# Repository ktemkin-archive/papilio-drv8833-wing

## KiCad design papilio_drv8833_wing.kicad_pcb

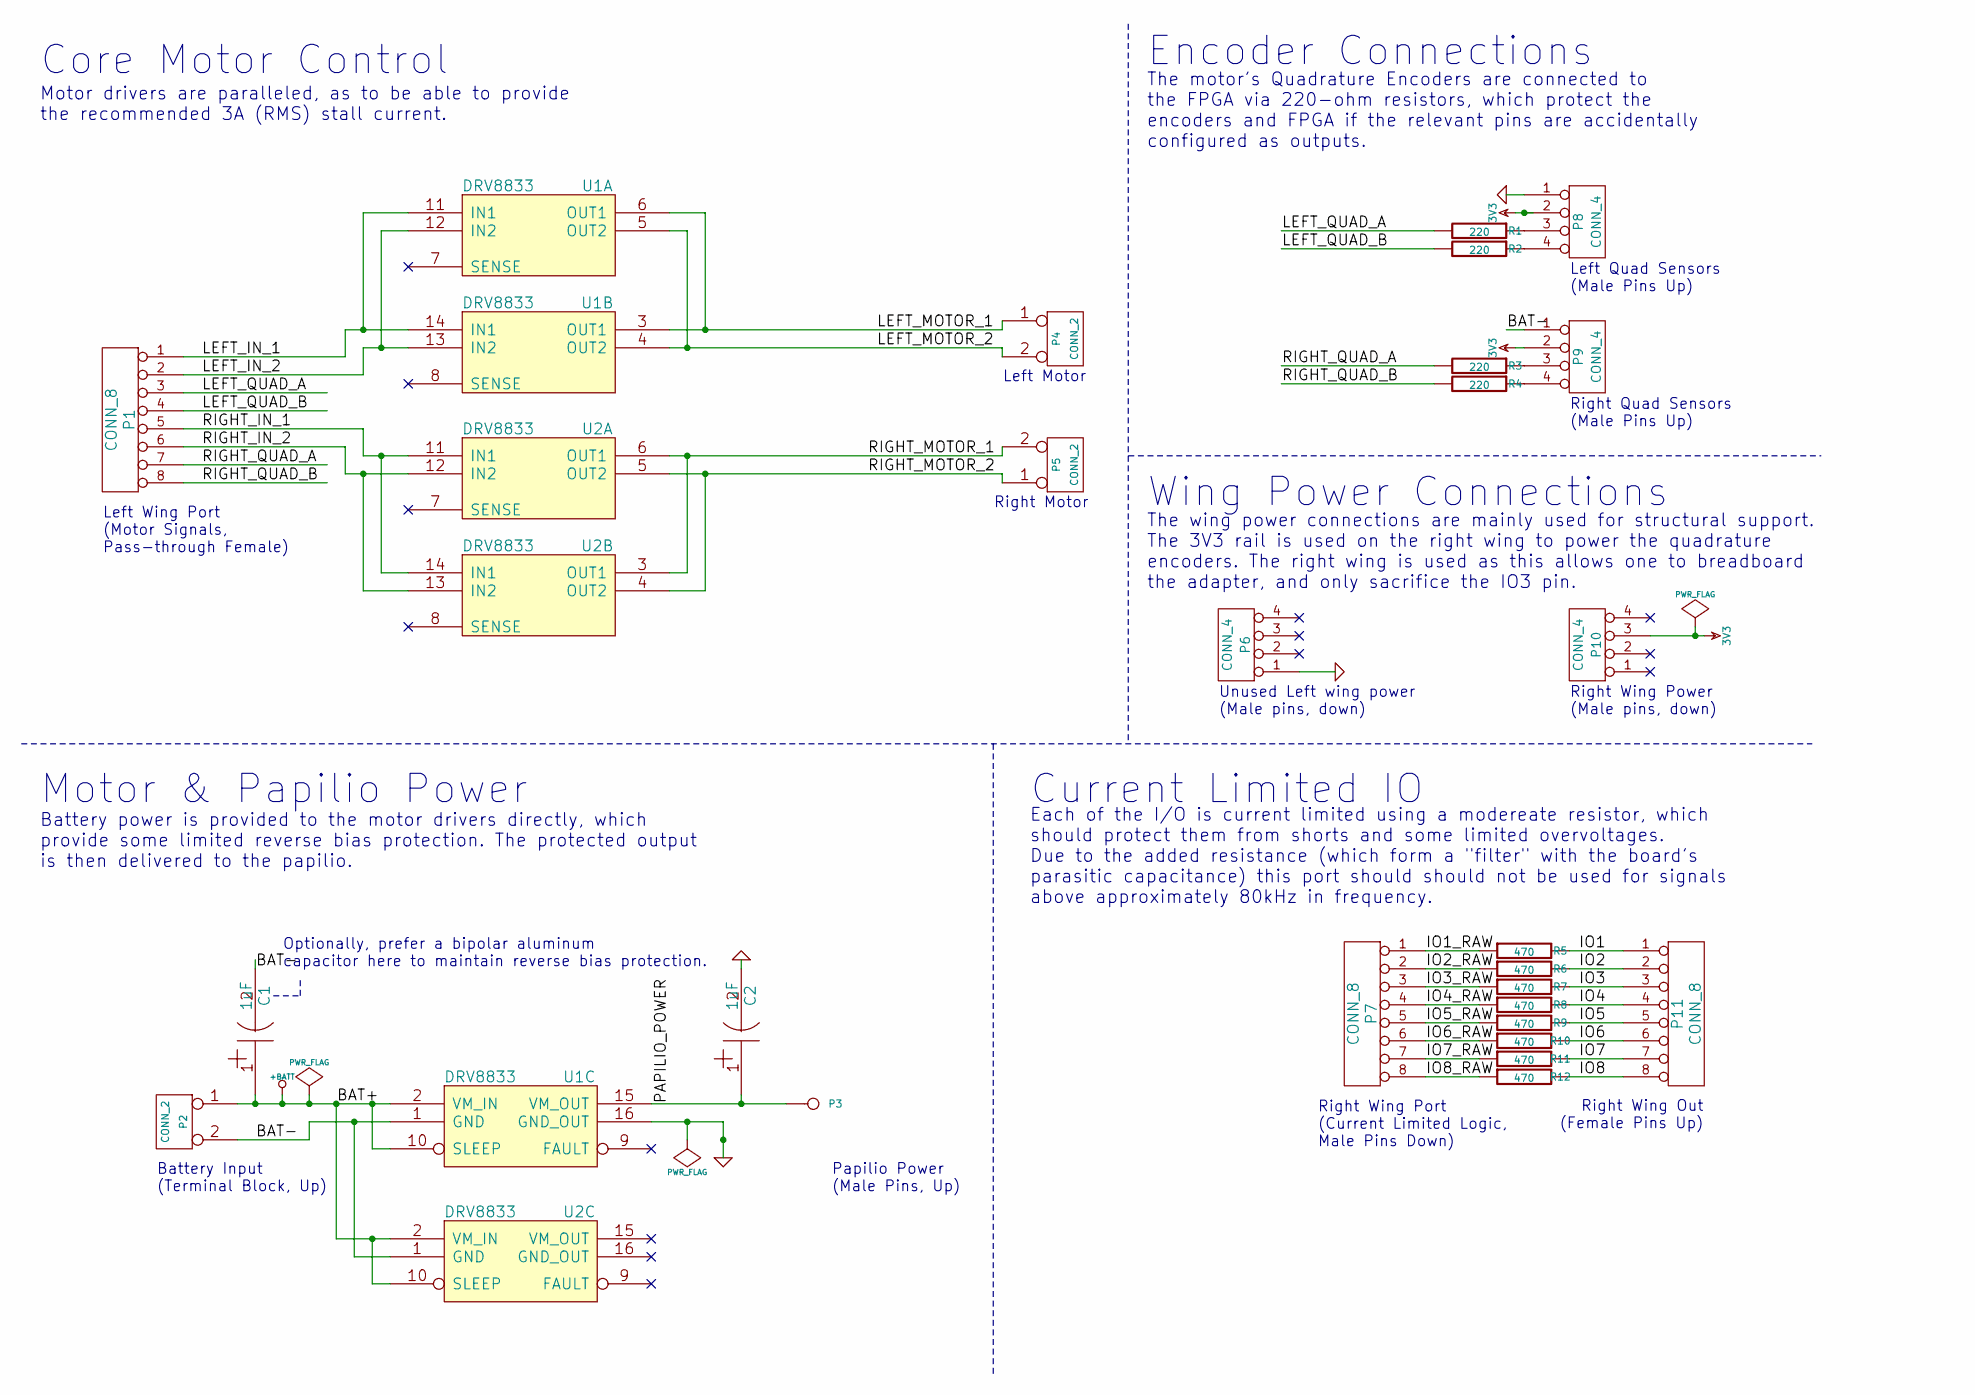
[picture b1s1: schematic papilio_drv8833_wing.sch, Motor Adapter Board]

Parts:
C1, C2: 1uF; Capacitor5x11RM2.5
P1, P7, P11: CONN_8; SIL-8
P2: CONN_2; terminal-block-D021B01LF
P3: CONN_1; SIL-1
P4, P5: CONN_2; rover5-motor
P6, P8, P9, P10: CONN_4; SIL-4
R1, R2, R3, R4: 220; Resistor_Horizontal_RM10mm
R5, R6, R7, R8, R9, R10, R11, R12: 470; Resistor_Horizontal_RM10mm
U1, U2: DRV8833; DRV8833-carrier

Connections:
3V3: P8.2, P9.2, P10.3
+BATT: C1.1, P2.1, U1.2 (VM_IN), U1.10 (SLEEP), U2.2 (VM_IN), U2.10 (SLEEP)
/BAT-: C1.2, P2.2 (PM), P9.1, U1.1 (GND), U2.1 (GND)
/IO1: P11.1, R5.2
/IO1_RAW: P7.1, R5.1
/IO2: P11.2, R6.2
/IO2_RAW: P7.2, R6.1
/IO3: P11.3, R7.2
/IO3_RAW: P7.3, R7.1
/IO4: P11.4, R8.2
/IO4_RAW: P7.4, R8.1
/IO5: P11.5, R9.2
/IO5_RAW: P7.5, R9.1
/IO6: P11.6, R10.2
/IO6_RAW: P7.6, R10.1
/IO7: P11.7, R11.2
/IO7_RAW: P7.7, R11.1
/IO8: P11.8, R12.2
/IO8_RAW: P7.8, R12.1
/LEFT_IN_1: P1.1, U1.11 (IN1), U1.14 (IN1)
/LEFT_IN_2: P1.2, U1.12 (IN2), U1.13 (IN2)
/LEFT_MOTOR_1: P4.1, U1.3 (OUT1), U1.6 (OUT1)
/LEFT_MOTOR_2: P4.2 (PM), U1.4 (OUT2), U1.5 (OUT2)
/LEFT_QUAD_A: P1.3, R1.2
/LEFT_QUAD_B: P1.4, R2.2
/PAPILIO_POWER: C2.1, P3.1, U1.15 (VM_OUT)
/RIGHT_IN_1: P1.5, U2.11 (IN1), U2.14 (IN1)
/RIGHT_IN_2: P1.6, U2.12 (IN2), U2.13 (IN2)
/RIGHT_MOTOR_1: P5.2 (PM), U2.3 (OUT1), U2.6 (OUT1)
/RIGHT_MOTOR_2: P5.1, U2.4 (OUT2), U2.5 (OUT2)
/RIGHT_QUAD_A: P1.7, R3.2
/RIGHT_QUAD_B: P1.8, R4.2
GND: C2.2, P6.1, P8.1, U1.16 (GND_OUT)
unnamed: P8.3, R1.1
unnamed: P8.4, R2.1
unnamed: P9.3, R3.1
unnamed: P9.4, R4.1

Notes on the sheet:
Right Wing Power (Male pins, down)
Left Wing Port (Motor Signals, Pass-through Female)
Left Quad Sensors (Male Pins Up)
Left Motor
Right Motor
Right Wing Port (Current Limited Logic, Male Pins Down)
Right Wing Out (Female Pins Up)
Right Quad Sensors (Male Pins Up)
Battery Input (Terminal Block, Up)
Papilio Power (Male Pins, Up)
Unused Left wing power (Male pins, down)
Core Motor Control
Motor drivers are paralleled, as to be able to provide the recommended 3A (RMS) stall current.
Motor & Papilio Power
Battery power is provided to the motor drivers directly, which provide some limited reverse bias protection. The protected output is then delivered to the papilio.
Encoder Connections
The motor's Quadrature Encoders are connected to the FPGA via 220-ohm resistors, which protect the encoders and FPGA if the relevant pins are accidentally configured as outputs.
Wing Power Connections
The wing power connections are mainly used for structural support. The 3V3 rail is used on the right wing to power the quadrature encoders. The right wing is used as this allows one to breadboard the adapter, and only sacrifice the IO3 pin.
Current Limited IO
Each of the I/O is current limited using a modereate resistor, which should protect them from shorts and some limited overvoltages. Due to the added resistance (which form a "filter" with the board's parasitic capacitance) this port should should not be used for signals above approximately 80kHz in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
Optionally, prefer a bipolar aluminum capacitor here to maintain reverse bias protection.

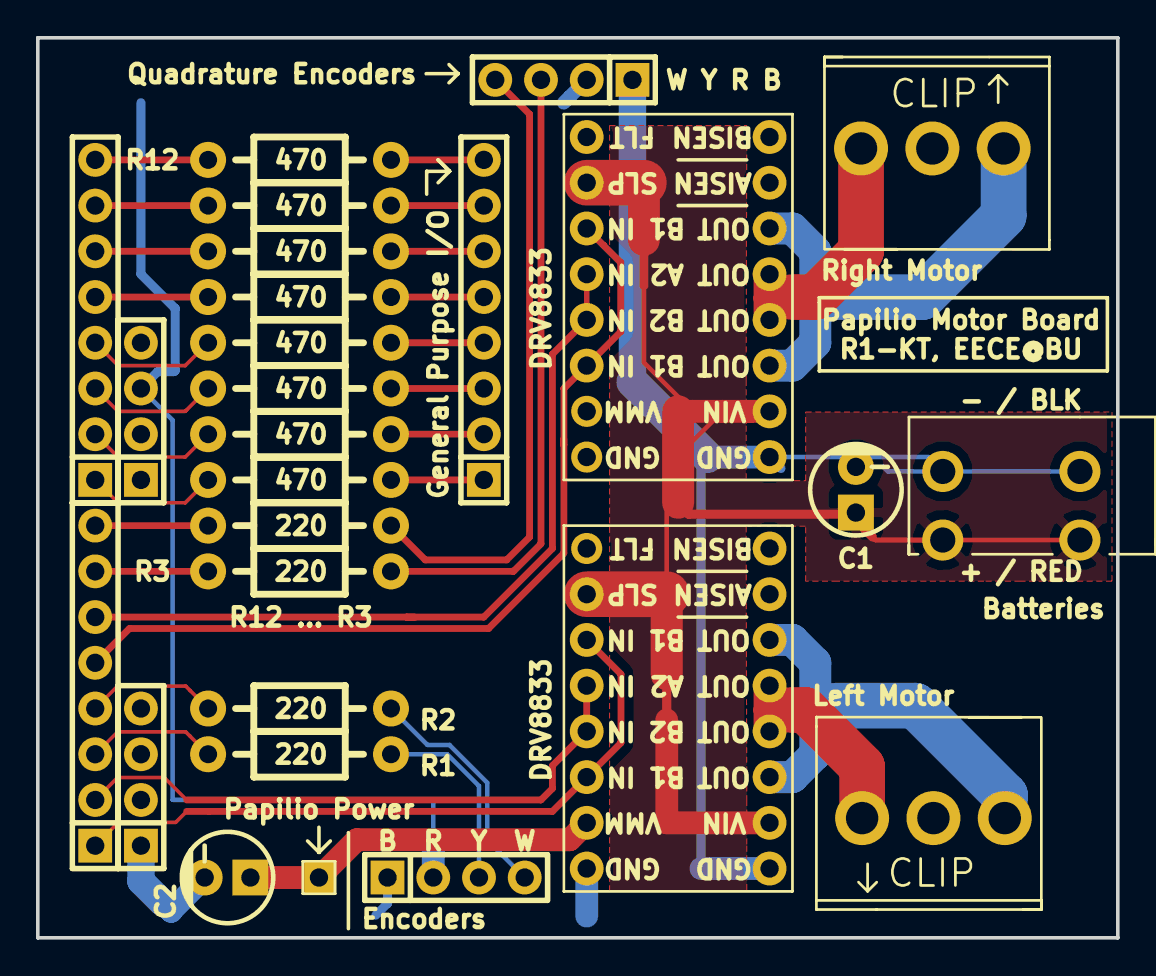
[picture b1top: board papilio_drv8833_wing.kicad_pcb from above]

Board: 2 copper layers, 60.0 x 50.0 mm, 27 parts (0 on the bottom side), 37 nets.

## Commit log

2015-10-08 Initial commit.
